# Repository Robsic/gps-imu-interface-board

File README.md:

# IMU_GPS_Blue_Pill — Placa IMU + GPS com Blue Pill (STM32)

Projeto KiCad (`IMU_board.kicad_sch` / `IMU_board.kicad_pcb`) para placa de IMU/GPS baseada em **OpenIMU300ZI** + **STM32 Blue Pill** + regulador **LM1117-3.3**.
Este README torna o projeto **portável para `git clone`** (sem dependências globais) e documenta as bibliotecas locais.

> Projeto pai: [`../README.md`](../README.md) · Datasheets: `../Imu datasheet connector/` · `Kicad-STM32-master/`

---

## 1. Estrutura e bibliotecas locais

Todas as libs não-padrão já estão **dentro do diretório do projeto** e são referenciadas via `${KIPRJMOD}` (pasta do `IMU_board.kicad_pro`). Após `git clone` o KiCad carrega automaticamente.

```text
IMU_GPS_Blue_Pill/
├── sym-lib-table          # 4 libs Legacy via ${KIPRJMOD}
├── fp-lib-table           # 4 libs KiCad via ${KIPRJMOD}
├── Kicad-STM32-master/    # YAAJ BluePill/BlackPill — symbols + footprints + 3D
│   ├── Symbols/YAAJ_BluePill_Part_Like_SWD_Breakout.lib
│   ├── Footprints/
│   ├── LM1117IMPX-3.3_NOPB(1)/   # footprint do LM1117-3.3 (nome com parênteses)
│   └── Packages3d/
├── imu_connector_female_2x10.pretty/   # conector IMU 2×10 fêmea
├── conn_gps_female_2x20.pretty/        # conector GPS 2×20 fêmea
├── RBS_stm32f103.pretty/                # footprint RBS STM32F103 (alternativo)
├── conn_02x10_top_bottom_imu.lib       # símbolo conector IMU 2×10
├── imu_conector.lib / imu_conector.dcm # símbolo conector IMU (legado)
├── RBS_stm32f103.lib / .dcm             # símbolo STM32F103RET6 (legado)
├── rbs02_components.lib                 # BD-STM32-AD etc.
└── IMU_board-cache.lib                  # cache legado (mantido p/ compatibilidade)
```

### sym-lib-table (corrigido para relativo)

```lisp
(lib (name "imu_conn") (type "Legacy") (uri "${KIPRJMOD}/conn_02x10_top_bottom_imu.lib") ...)
(lib (name "Blue_pill") (type "Legacy") (uri "${KIPRJMOD}/Kicad-STM32-master/Symbols/YAAJ_BluePill_Part_Like_SWD_Breakout.lib") ...)
(lib (name "YAAJ_BluePill_Part_Like_SWD_Breakout") (type "Legacy") (uri "${KIPRJMOD}/Kicad-STM32-master/Symbols/YAAJ_BluePill_Part_Like_SWD_Breakout.lib") ...)
(lib (name "IMU_board-cache") (type "Legacy") (uri "${KIPRJMOD}/IMU_board-cache.lib") ...)
```

Antes havia `IMU_GPS_Blue_Pill/` duplicado em `imu_conn` e caminho absoluto `/home/ryan/.../IMU_board-cache.lib` — agora relativo.

### fp-lib-table

```lisp
(lib (name "Blue_pill") (type "KiCad") (uri "${KIPRJMOD}/Kicad-STM32-master/Footprints") ...)
(lib (name "LM117IMPX3.3") (type "KiCad") (uri "${KIPRJMOD}/Kicad-STM32-master/LM1117IMPX-3.3_NOPB(1)") ...)
(lib (name "imu_connector_female_2x10") (type "KiCad") (uri "${KIPRJMOD}/imu_connector_female_2x10.pretty") ...)
(lib (name "conn_gps_female_2x20") (type "KiCad") (uri "${KIPRJMOD}/conn_gps_female_2x20.pretty") ...)
```

> **Aviso nome com `()`**: `LM1117IMPX-3.3_NOPB(1)` contém parênteses. Funciona, mas pode quebrar scripts `git` em Windows. Se der erro, renomeie a pasta para `LM1117IMPX-3.3_NOPB_1` e atualize `fp-lib-table:4`.

---

## 2. Como usar após `git clone` — zero configuração

**Requisitos:** KiCad 7+ (testado 10.0.4).

```bash
git clone <URL> && cd Robsic---imu-board-design-with-gps-master/IMU_GPS_Blue_Pill
kicad IMU_board.kicad_pro   # ou File → Open Project
```

O KiCad carrega `sym-lib-table` / `fp-lib-table` locais automaticamente (`Preferences → Manage Symbol/Footprint Libraries → Project Specific`).

- Não mexa em `Kicad-STM32-master/` — já é a lib YAAJ oficial (GitHub `yet-another-average-joe/Kicad-STM32`).
- `IMU_board.kicad_pcb` e conectores `2×10` / `2×20` resolvem sem instalação global.

**PCB não foi alterado eletricamente** nesta migração (só `sym-lib-table:3,6`). Resíduos `D:/Users/admin/...` em `Kicad-STM32-master/Footprints/*.kicad_mod:114` e `IMU_board.kicad_pcb:6957` são legados do YAAJ e não afetam fabricação.

---

## 3. Adicionar nova biblioteca (ex.: Molex / Bourns para bornes)

Para manter o padrão de `treadle` e `Steer/Estercamento`:

```bash
cp -a /home/ryan/Documentos/Robsic\ Carrinho/pedais/treadle/libs/Connector_Molex ./libs/Connector_Molex
# em fp-lib-table adicione:
# (lib (name "Connector_Molex") (type "KiCad") (uri "${KIPRJMOD}/libs/Connector_Molex/Connector_Molex.pretty") ...)
git add libs/Connector_Molex fp-lib-table
```

Mapeamento Molex usado nos outros projetos (se precisar aqui):
- 2 pinos → `Connector_Molex:Molex_Micro-Fit_3.0_Molex_Micro-Fit_3.0_Header_Vertical_1x02_P3.00mm_Snap-in_Plastic_Peg_TH_436500215` (fallback genérico `...1x02...`)
- 3 pinos → `...1x03...436500315`
- 4 pinos → `...1x04...436500415`

---

## 5. Checklist de portabilidade

- [x] `grep -r "/home/ryan" sym-lib-table fp-lib-table` vazio
- [x] `ls Kicad-STM32-master/Symbols/YAAJ_BluePill_Part_Like_SWD_Breakout.lib` existe
- [x] Abrir `IMU_board.kicad_sch` → ERC 0 erros de lib
- [x] Abrir `IMU_board.kicad_pcb` → DRC sem "missing footprint"

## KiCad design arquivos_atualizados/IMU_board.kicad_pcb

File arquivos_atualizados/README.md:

# Placa GPS/IMU e interface de encoders — RobSIC

Placa de aquisição e comunicação para o carrinho elétrico RobSIC, baseada em módulo STM32F103/Blue Pill. O hardware integra alimentação de 12 V, interface CAN, duas entradas de encoder incremental diferencial A/B/Z, conexão para módulo IMU, conexão para módulo GPS e interfaces de programação/depuração.

> **Status:** projeto em desenvolvimento e **não liberado para fabricação**. O relatório DRC fornecido registra 20 violações: 12 de máscara de solda, 5 de clearance, 1 texto espelhado e 2 conflitos de silk sobre cobre.

> **Simulação funcional:** a integração GPS/NMEA, UART, pacote ACEINNA `e2`, CRC e estímulos de IMU/encoders foi exercitada no Proteus 9.1. CAN, desempenho dos sensores reais e comportamento elétrico permanecem pendentes de bancada.

> **Atualização de hardware — 09/09/2026:** esquemático e PCB atualizados com conectores Molex Micro-Fit 3.0, biblioteca local de footprints e referências portáveis via `${KIPRJMOD}`.

## Arquitetura

```mermaid
flowchart TD
    PWR["12 V — J1"] --> DCDC["TSR2-2450 — 5 V"]
    DCDC --> LDO["LM1117-3.3 — 3,3 V"]
    LDO --> MCU["Blue Pill / STM32F103"]
    CAN["CANH/CANL — J1"] <-->|"SN65HVD230"| MCU
    ENC["2 encoders A/B/Z"] -->|"TVS + AM26LV32"| MCU
    MCU <-->|"UART"| IMU["Módulo IMU — J5"]
    IMU <-->|"UART2"| GPS["Módulo GPS — J4"]
```

## Simulação e validação no Proteus

O ensaio utiliza duas Blue Pills:

- `U1`: controlador principal da placa;
- `U2`: emulador funcional do OpenIMU300ZI;
- `VGPS`: fonte de mensagens NMEA;
- dois terminais virtuais para observar o NMEA a 9600 baud e o diagnóstico da U1 a 115200 baud.

Resultados confirmados na simulação:

- recepção das mensagens NMEA `GGA`, `RMC` e `GSA`;
- detecção de `GPS=FIX` e hemisférios `NW`;
- transmissão U2 → U1 a 115200 baud;
- recepção de pacotes ACEINNA `e2` com `CRC=OK`;
- contador de pacotes crescente, `CRC_ERR=0` e `RX_OVF=0`;
- transporte de dados sintéticos de orientação, aceleração e encoders.

Limitações conhecidas:

- a conversão decimal de latitude/longitude não é confiável no modelo VSM de terceiros da Blue Pill; as coordenadas NMEA de entrada estão corretas;
- o CAN não é suportado de forma confiável por esse modelo e aparece como `CAN=NA(PROTEUS)`;
- os dados de IMU e encoders são estímulos funcionais, não medições de sensores físicos.

Arquivos, firmware e procedimento completo: [simulação Proteus](simulation/proteus/README.md).

## Características extraídas dos arquivos

- KiCad: gerador `10.0`.
- Dimensão do contorno: `111 mm × 79 mm`.
- Componentes posicionados: 31.
- Roteamento: 415 segmentos e 50 vias.
- Alimentação de entrada nominal indicada: `+12 V`.
- Conversão: `TSR2-2450` para 5 V e `LM1117-3.3` para 3,3 V.
- CAN: `SN65HVD230`, com terminação de 120 Ω.
- Encoders: dois canais diferenciais A/B/Z, protegidos por `SRV05-4` e recebidos por `AM26LV32`.
- Controlador: módulo Blue Pill/STM32F103.

## Interfaces principais

| Conector | Função | Resumo |
|---|---|---|
| J1 | Alimentação e CAN | `+12 V`, `CANH`, `CANL`, `GND` |
| J2 | Encoder com nets `Esq` | `GND`, `+5 V`, pares diferenciais A/B/Z |
| J3 | Encoder com nets `Dir` | `GND`, `+5 V`, pares diferenciais A/B/Z |
| J4 | Módulo GPS | UART2, `+3.3V_GPS`, `GND` |
| J5 | Módulo IMU | UART, UART2 do GPS, SWD, reset, 3,3 V e GND |
| JTAG_IMU1 | Depuração da IMU | `NRST`, `SWDIO`, `SWCLK`; pino 4 está sem GND |

> Os valores visuais `J_Dir` e `J_Esq` estão trocados em relação aos nomes das redes do PCB: J2 carrega sinais `*_Esq` e J3 carrega sinais `*_Dir`. Use as redes e a tabela de pinagem como referência até corrigir a serigrafia/valor.

## Abrindo o projeto

1. Instale o KiCad 10 ou versão compatível mais recente.
2. Baixe a pasta completa, preservando todas as subpastas de footprints e `Kicad-STM32-master/`.
3. Abra `IMU_board.kicad_pro`.
4. Confira `fp-lib-table`; todas as entradas devem usar `${KIPRJMOD}` e caminhos relativos.
5. Confirme que `sym-lib-table` e `fp-lib-table` foram carregados como bibliotecas específicas do projeto; as referências incluídas já usam caminhos relativos via `${KIPRJMOD}`.
6. Abra as folhas hierárquicas `IMU.kicad_sch`, `GPS.kicad_sch` e `stm32f103.kicad_sch` pelo esquema principal.
7. Execute ERC e DRC novamente; não gere Gerbers enquanto houver violações.

O modelo 3D local da Blue Pill usa o arquivo WRL versionado. O STEP completo, com 92,6 MB, permanece na pasta de origem do Google Drive para evitar inflar o repositório.

## Estrutura recomendada para o GitHub

```text
gps-imu-interface-board/
├── README.md
├── BOM.csv
├── .gitignore
├── hardware/
│   ├── IMU_board.kicad_pro
│   ├── IMU_board.kicad_sch
│   ├── IMU_board.kicad_pcb
│   ├── GPS.kicad_sch
│   ├── IMU.kicad_sch
│   ├── stm32f103.kicad_sch
│   ├── fp-lib-table
│   ├── sym-lib-table
│   └── libraries/
├── firmware/
├── docs/
│   ├── HARDWARE.md
│   ├── FIRMWARE.md
│   ├── VALIDATION.md
│   └── GITHUB.md
├── manufacturing/
└── legacy/
```

## Documentos

- [Hardware e pinagem](docs/HARDWARE.md)
- [Firmware e mapa do STM32](docs/FIRMWARE.md)
- [Validação e DRC](docs/VALIDATION.md)
- [Preparação e envio ao GitHub](docs/GITHUB.md)
- [Portabilidade e bibliotecas locais do KiCad](docs/KICAD_PORTABILITY.md)
- [Documentação técnica original da placa](DOCUMENTACAO_GPS.md)
- [Simulação funcional no Proteus 9.1](simulation/proteus/README.md)
- [Lista de materiais](BOM.csv)

## Pendências críticas

- eliminar as 20 violações do DRC fornecido;
- corrigir a identificação J2/J3;
- adicionar GND ao cabeçalho de programação da IMU ou documentar ponto de referência externo;
- confirmar o footprint polarizado de C4, marcado como 100 nF;
- confirmar pinagem física dos módulos GPS e IMU com os respectivos datasheets;
- desenvolver o firmware de produção, configuração STM32CubeMX/CubeIDE e protocolo CAN; o firmware incluído em `simulation/` é exclusivo para validação funcional;
- validar entrada de 12 V e proteções para uso veicular;
- gerar pacote de fabricação somente depois da liberação.

## Licença

Nenhuma licença foi definida. Antes de tornar o repositório público, escolha licenças compatíveis para hardware, firmware, bibliotecas de terceiros e documentação.

## Responsável

Vinícius Corcínio Silva — projeto RobSIC.

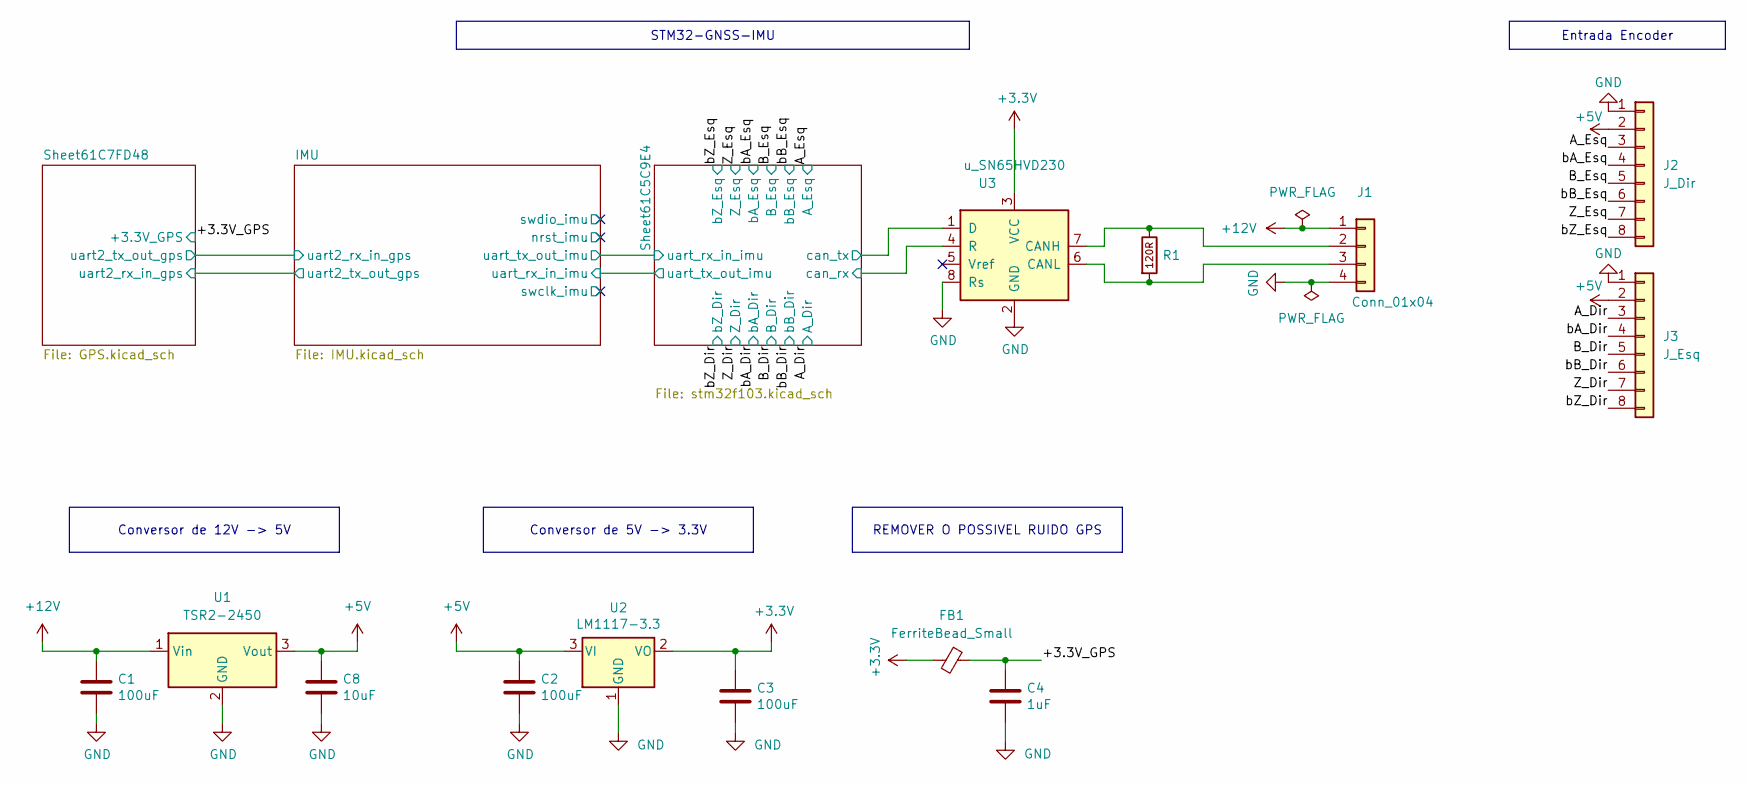
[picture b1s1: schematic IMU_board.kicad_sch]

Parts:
C1, C2, C3: 100uF; CP_Radial_D5.0mm_P2.50mm
C4: 1uF; C_0805_2012Metric
C8: 10uF; CP_Radial_D5.0mm_P2.50mm
FB1: FerriteBead_Small; L_0805_2012Metric_Pad1.05x1.20mm_HandSolder
J1: Conn_01x04; Molex_Micro-Fit_3.0_Molex_Micro-Fit_3.0_Header_Vertical_1x0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
J2: J_Dir; Molex_Micro-Fit_3.0_Molex_Micro-Fit_3.0_Header_Vertical_1x0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
J3: J_Esq; Molex_Micro-Fit_3.0_Molex_Micro-Fit_3.0_Header_Vertical_1x0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
R1: r_120; R_0805_2012Metric_Pad1.20x1.40mm_HandSolder; MPN ERJ-P06F1200V
U1: TSR2-2450; Converter_DCDC_TRACO_TSR2-xxxx_THT
U2: LM1117-3.3; LM1117IMP_3.3_NOPB
U3: u_SN65HVD230; SOIC-8_3.9x4.9mm_P1.27mm; MPN SN65HVD230MDREP

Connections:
+3.3V: C3.1, FB1.2, U2.2 (VO), U3.3 (VCC); also elsewhere on the board
+5V: C2.1, C8.1, J2.2, J3.2, U1.3 (Vout), U2.3 (VI); also elsewhere on the board
+12V: C1.1, J1.1, U1.1 (Vin)
/+3.3V_GPS: C4.1, FB1.1; also elsewhere on the board
/A_Dir: J3.3; also elsewhere on the board
/A_Esq: J2.3; also elsewhere on the board
/B_Dir: J3.5; also elsewhere on the board
/B_Esq: J2.5; also elsewhere on the board
/Sheet61C5C9E4/can_rx: U3.4 (R); also elsewhere on the board
/Sheet61C5C9E4/can_tx: U3.1 (D); also elsewhere on the board
/Z_Dir: J3.7; also elsewhere on the board
/Z_Esq: J2.7; also elsewhere on the board
/bA_Dir: J3.4; also elsewhere on the board
/bA_Esq: J2.4; also elsewhere on the board
/bB_Dir: J3.6; also elsewhere on the board
/bB_Esq: J2.6; also elsewhere on the board
/bZ_Dir: J3.8; also elsewhere on the board
/bZ_Esq: J2.8; also elsewhere on the board
GND: C1.2, C2.2, C3.2, C4.2, C8.2, J1.4, J2.1, J3.1, U1.2 (GND), U2.1 (GND), U3.2 (GND), U3.8 (Rs); also elsewhere on the board
unnamed: J1.2, R1.1, U3.7 (CANH)
unnamed: J1.3, R1.2, U3.6 (CANL)

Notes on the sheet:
Conversor de 12V -> 5V
REMOVER O POSSIVEL RUIDO GPS
Entrada Encoder
Conversor de 5V -> 3.3V
STM32-GNSS-IMU

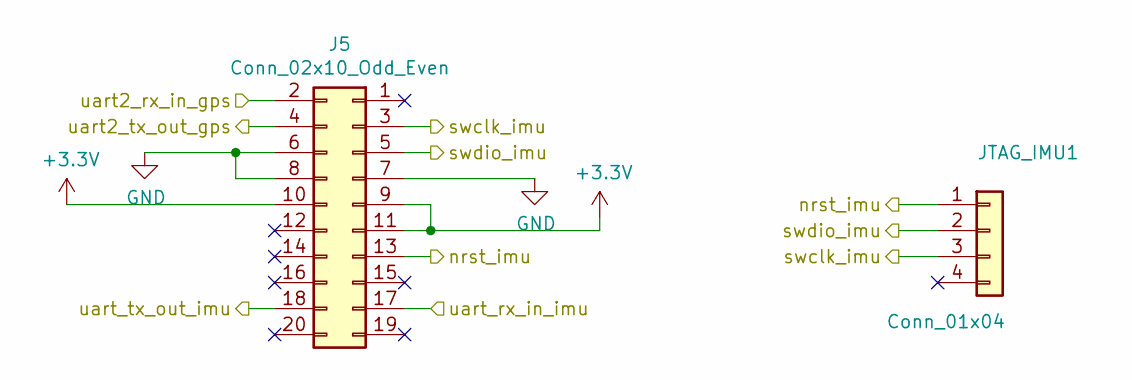
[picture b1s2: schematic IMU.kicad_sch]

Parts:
J5: Conn_02x10_Odd_Even; imu_connector_female_2x10
JTAG_IMU1: Conn_01x04; Molex_Micro-Fit_3.0_Molex_Micro-Fit_3.0_Header_Vertical_1x0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

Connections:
+3.3V: J5.9, J5.10, J5.11; also elsewhere on the board
/IMU/nrst_imu: J5.13, JTAG_IMU1.1
/IMU/swclk_imu: J5.3, JTAG_IMU1.3
/IMU/swdio_imu: J5.5, JTAG_IMU1.2
/IMU/uart2_rx_in_gps: J5.2; also elsewhere on the board
/IMU/uart2_tx_out_gps: J5.4; also elsewhere on the board
/IMU/uart_rx_in_imu: J5.17; also elsewhere on the board
/IMU/uart_tx_out_imu: J5.18; also elsewhere on the board
GND: J5.6, J5.7, J5.8; also elsewhere on the board

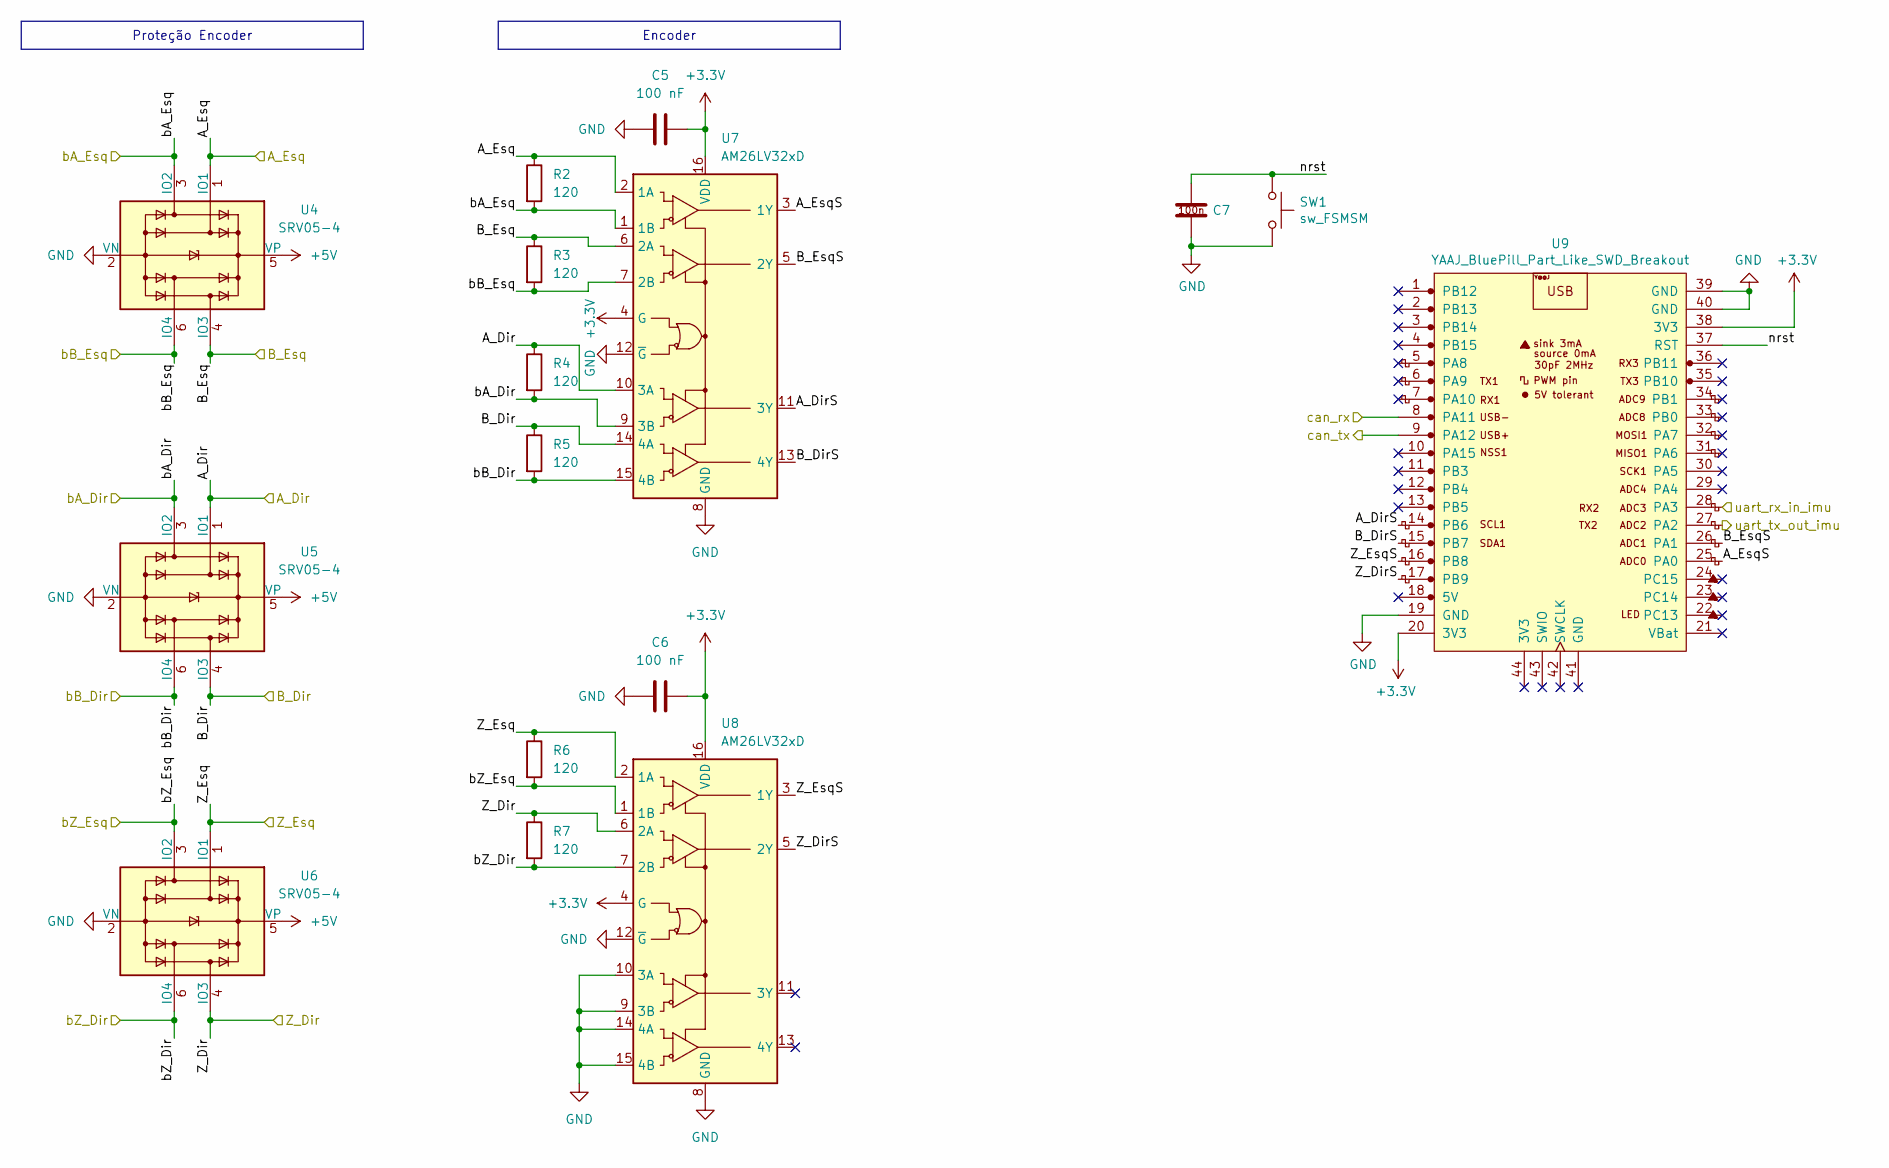
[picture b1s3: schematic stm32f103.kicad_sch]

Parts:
C5, C6: 100 nF; C_0805_2012Metric_Pad1.18x1.45mm_HandSolder
C7: c_100n; C_0805_2012Metric_Pad1.18x1.45mm_HandSolder; MPN 08055C104KAT2A
R2, R3, R4, R5, R6, R7: 120; R_0805_2012Metric_Pad1.20x1.40mm_HandSolder
SW1: sw_FSMSM; SW_SPST_FSMSM; MPN FSMSM
U4, U5, U6: SRV05-4; SOT-23-6_Handsoldering
U7, U8: AM26LV32xD; SOIC-16_3.9x9.9mm_P1.27mm
U9: YAAJ_BluePill_Part_Like_SWD_Breakout; YAAJ_BluePill_SWD_2

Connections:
+3.3V: C5.2, C6.2, U7.4 (G), U7.16 (VDD), U8.4 (G), U8.16 (VDD), U9.20 (3V3), U9.38 (3V3); also elsewhere on the board
+5V: U4.5 (VP), U5.5 (VP), U6.5 (VP); also elsewhere on the board
/A_Dir: R4.1, U5.1 (IO1), U7.10 (3A); also elsewhere on the board
/A_Esq: R2.1, U4.1 (IO1), U7.2 (1A); also elsewhere on the board
/B_Dir: R5.1, U5.4 (IO3), U7.14 (4A); also elsewhere on the board
/B_Esq: R3.1, U4.4 (IO3), U7.6 (2A); also elsewhere on the board
/IMU/uart_rx_in_imu: U9.27 (PA2); also elsewhere on the board
/IMU/uart_tx_out_imu: U9.28 (PA3); also elsewhere on the board
/Sheet61C5C9E4/A_DirS: U7.11 (3Y), U9.14 (PB6)
/Sheet61C5C9E4/A_EsqS: U7.3 (1Y), U9.25 (PA0)
/Sheet61C5C9E4/B_DirS: U7.13 (4Y), U9.15 (PB7)
/Sheet61C5C9E4/B_EsqS: U7.5 (2Y), U9.26 (PA1)
/Sheet61C5C9E4/Z_DirS: U8.5 (2Y), U9.17 (PB9)
/Sheet61C5C9E4/Z_EsqS: U8.3 (1Y), U9.16 (PB8)
/Sheet61C5C9E4/can_rx: U9.8 (PA11); also elsewhere on the board
/Sheet61C5C9E4/can_tx: U9.9 (PA12); also elsewhere on the board
/Sheet61C5C9E4/nrst: C7.1, SW1.1, U9.37 (RST)
/Z_Dir: R7.1, U6.4 (IO3), U8.6 (2A); also elsewhere on the board
/Z_Esq: R6.1, U6.1 (IO1), U8.2 (1A); also elsewhere on the board
/bA_Dir: R4.2, U5.3 (IO2), U7.9 (3B); also elsewhere on the board
/bA_Esq: R2.2, U4.3 (IO2), U7.1 (1B); also elsewhere on the board
/bB_Dir: R5.2, U5.6 (IO4), U7.15 (4B); also elsewhere on the board
/bB_Esq: R3.2, U4.6 (IO4), U7.7 (2B); also elsewhere on the board
/bZ_Dir: R7.2, U6.6 (IO4), U8.7 (2B); also elsewhere on the board
/bZ_Esq: R6.2, U6.3 (IO2), U8.1 (1B); also elsewhere on the board
GND: C5.1, C6.1, C7.2, SW1.2, U4.2 (VN), U5.2 (VN), U6.2 (VN), U7.8 (GND), U7.12 (~G), U8.8 (GND), U8.9 (3B), U8.10 (3A), U8.12 (~G), U8.14 (4A), U8.15 (4B), U9.19 (GND), U9.39 (GND), U9.40 (GND); also elsewhere on the board

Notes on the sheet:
Encoder
Proteção Encoder

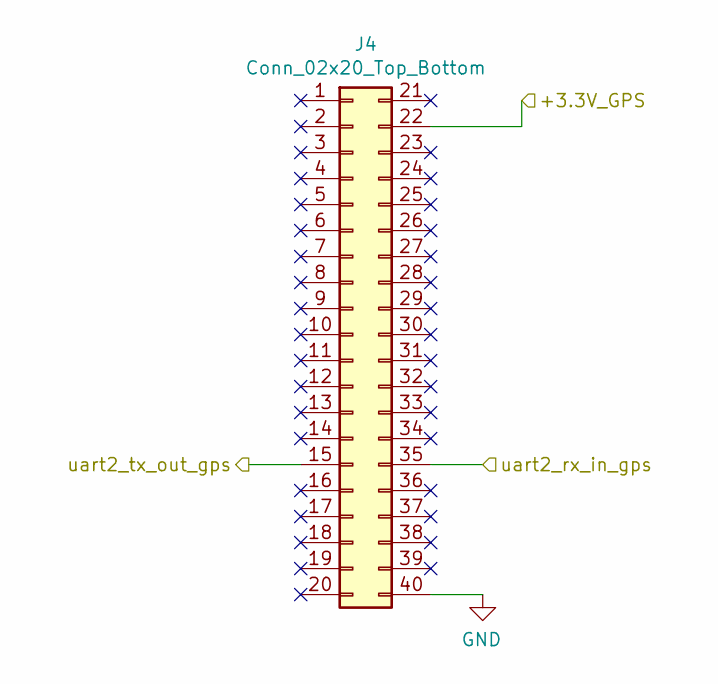
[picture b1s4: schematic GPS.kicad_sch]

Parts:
J4: Conn_02x20_Top_Bottom; conn_gps_female_2x20

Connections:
/+3.3V_GPS: J4.22; also elsewhere on the board
/IMU/uart2_rx_in_gps: J4.15; also elsewhere on the board
/IMU/uart2_tx_out_gps: J4.35; also elsewhere on the board
GND: J4.40; also elsewhere on the board

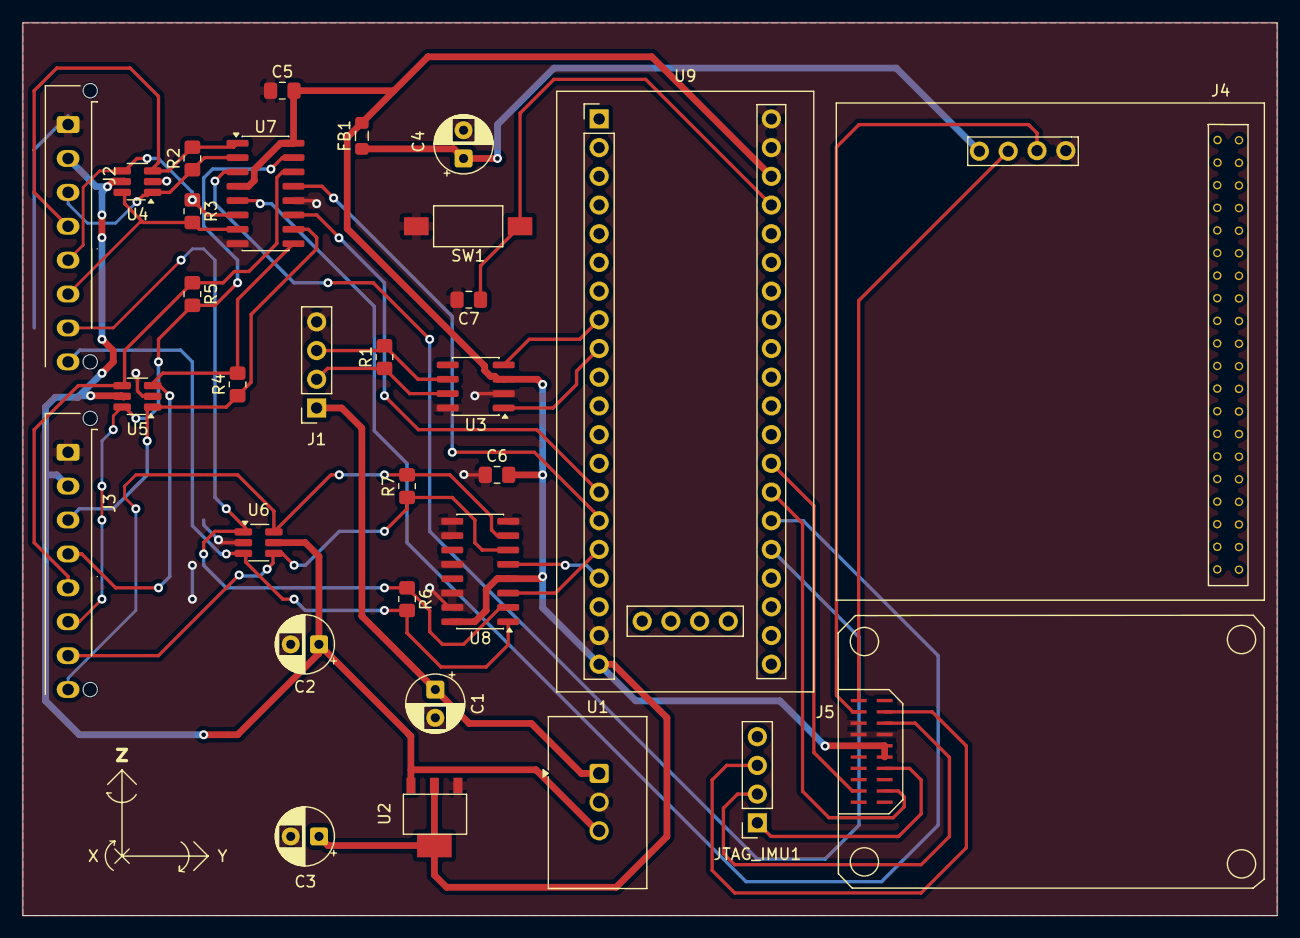
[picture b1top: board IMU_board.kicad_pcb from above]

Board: 4 copper layers, 111.0 x 79.0 mm, 31 parts (0 on the bottom side), 35 nets.

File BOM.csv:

Item,Referencias,Quantidade,Valor/Componente,Footprint,Observacao
1,U9,1,Blue Pill STM32F103,Blue_pill:YAAJ_BluePill_SWD_2,Confirmar variante exata do módulo e orientação
2,U1,1,TSR2-2450,Converter_DCDC:Converter_DCDC_TRACO_TSR2-xxxx_THT,Conversor 12 V para 5 V
3,U2,1,LM1117-3.3,LM117IMPX3.3:LM1117IMP_3.3_NOPB,Regulador 5 V para 3.3 V
4,U3,1,SN65HVD230,Package_SO:SOIC-8_3.9x4.9mm_P1.27mm,Transceptor CAN 3.3 V
5,U4-U6,3,SRV05-4,Package_TO_SOT_SMD:SOT-23-6_Handsoldering,Proteção dos pares de encoder; revisar máscara de solda
6,U7-U8,2,AM26LV32xD,Package_SO:SOIC-16_3.9x9.9mm_P1.27mm,Receptores diferenciais 3.3 V
7,C1,1,22 uF,Capacitor_THT:CP_Radial_D5.0mm_P2.50mm,Filtro de +12 V
8,C2,1,10 uF,Capacitor_THT:CP_Radial_D5.0mm_P2.50mm,Filtro de +5 V
9,C3,1,100 uF,Capacitor_THT:CP_Radial_D5.0mm_P2.50mm,Filtro de +3.3 V
10,C4,1,100 nF,Capacitor_THT:CP_Radial_D5.0mm_P2.50mm,Revisar valor versus footprint polarizado
11,C5-C6,2,100 nF,Capacitor_SMD:C_0805_2012Metric_HandSolder,Desacoplamento de +3.3 V
12,C7,1,100 nF,Capacitor_SMD:C_0805_2012Metric_HandSolder,Reset NRST para GND
13,FB1,1,Ferrite bead 0805,Inductor_SMD:L_0805_2012Metric_HandSolder,Filtro da alimentação do GPS; definir impedância e corrente
14,R1-R7,7,120 Ohm,Resistor_SMD:R_0805_2012Metric_HandSolder,Terminação CAN e seis pares diferenciais
15,SW1,1,FSMSM,Button_Switch_SMD:SW_SPST_FSMSM,Reset do STM32
16,J1,1,PinSocket 1x04 2.54 mm,Connector_PinSocket_2.54mm:PinSocket_1x04,12 V CANH CANL GND
17,J2-J3,2,PinSocket 1x08 2.54 mm,Connector_PinSocket_2.54mm:PinSocket_1x08,Entradas dos dois encoders
18,J4,1,Conector GPS 2x20,conn_gps_female_2x20:conn_gps_female_2x20,Footprint customizado
19,J5,1,Conector IMU 2x10,imu_connector_female_2x10:imu_connector_female_2x10,Footprint customizado
20,JTAG_IMU1,1,PinSocket 1x04 2.54 mm,Connector_PinSocket_2.54mm:PinSocket_1x04,Pino 4 sem conexão; revisar GND
